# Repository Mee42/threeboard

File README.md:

## Threeboard

The v1 threeboard has been fully assembled and firmware is currently in developement. 
Firmware is in the `code/` directory and is written in C.

### KiCad instructions
PCB files are in the `pcb/` directory. Threeboard is designed on an ATSAMD21E17A arm microcontroller. A v2 board is in development

Both 
[random parts](https://github.com/ai03-2725/random-keyboard-parts.pretty)
and
[mx switch footprint](https://github.com/ai03-2725/MX_Alps_Hybrid.pretty)
are dependencies for the kicad files.

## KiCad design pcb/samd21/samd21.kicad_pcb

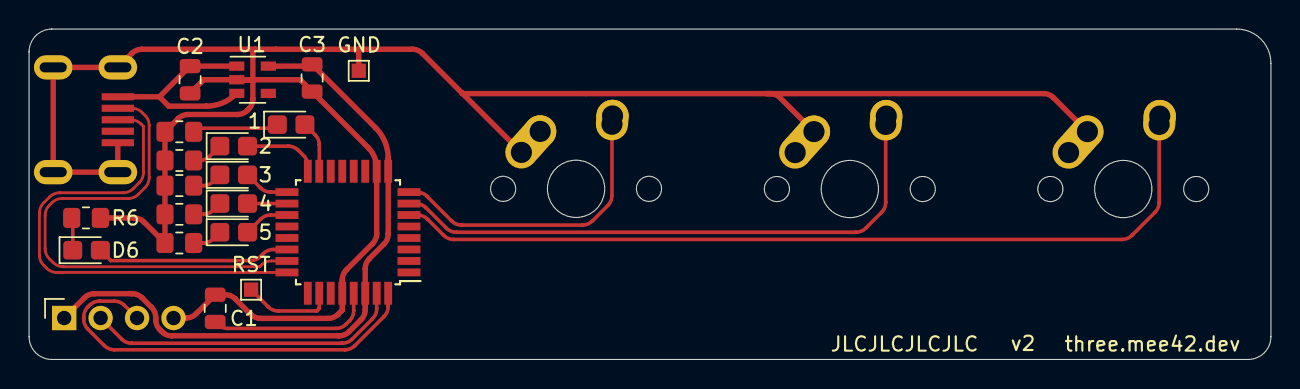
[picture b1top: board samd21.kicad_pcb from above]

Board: 2 copper layers, 86.5 x 23.0 mm, 24 parts (0 on the bottom side), 24 nets.

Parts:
1, 2, 3, 4, 5: LED; LED_0805_2012Metric_Castellated
C1, C2, C3: 1uF; C_0805_2012Metric
D6: LED; LED_0805_2012Metric_Castellated
GND: TestPoint; TestPoint_Pad_1.0x1.0mm
J1: Conn_01x04_Male; PinSocket_1x04_P2.54mm_Vertical
MX1, MX2, MX3: MX-NoLED; MX-1U-NoLED
R1, R2, R3, R4, R5, R6: 1.5K; R_0805_2012Metric_Pad1.20x1.40mm_HandSolder
RST: TestPoint; TestPoint_Pad_1.0x1.0mm
U1: TLV70033_SOT23-5; SOT-23-5
U2: ATSAMD21E17A-A; TQFP-32_7x7mm_P0.8mm
USB1: Molex-0548190589

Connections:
+3V3: C3.1, J1.1, U1.5 (OUT), U2.9 (VDDANA), U2.30 (VDDIN)
/5V: C2.1, U1.1 (IN), U1.3 (EN), USB1.5 (VBUS)
D+: U2.24 (PA25), USB1.3 (D+)
D-: U2.23 (PA24), USB1.4 (D-)
GND: C1.1, C2.2, C3.2, GND.1, J1.4, MX1.1 (COL), MX2.1 (COL), MX3.1 (COL), R1.2, R2.2, R3.2, R4.2, R5.2, R6.2, U1.2 (GND), U2.10 (GND), U2.28 (GND), USB1.1 (GND), USB1.6 (SHIELD)
KEY1: MX1.2 (ROW), U2.8 (PA07)
KEY2: MX2.2 (ROW), U2.7 (PA06)
KEY3: MX3.2 (ROW), U2.6 (PA05)
LED0: 1.2 (A), U2.15 (PA14)
LED1: 2.2 (A), U2.16 (PA15)
LED2: 3.2 (A), U2.17 (PA16)
LED3: 4.2 (A), U2.18 (PA17)
LED4: 5.2 (A), U2.19 (PA18)
LED5: D6.2 (A), U2.22 (PA23)
unnamed: C1.2, U2.29 (VDDCORE)
unnamed: 1.1 (K), R1.1
unnamed: 2.1 (K), R2.1
unnamed: 3.1 (K), R3.1
unnamed: 4.1 (K), R4.1
unnamed: 5.1 (K), R5.1
unnamed: D6.1 (K), R6.1
unnamed: RST.1, U2.26 (~RESET)
SWCLK: J1.2, U2.31 (PA30)
SWDIO: J1.3, U2.32 (PA31)

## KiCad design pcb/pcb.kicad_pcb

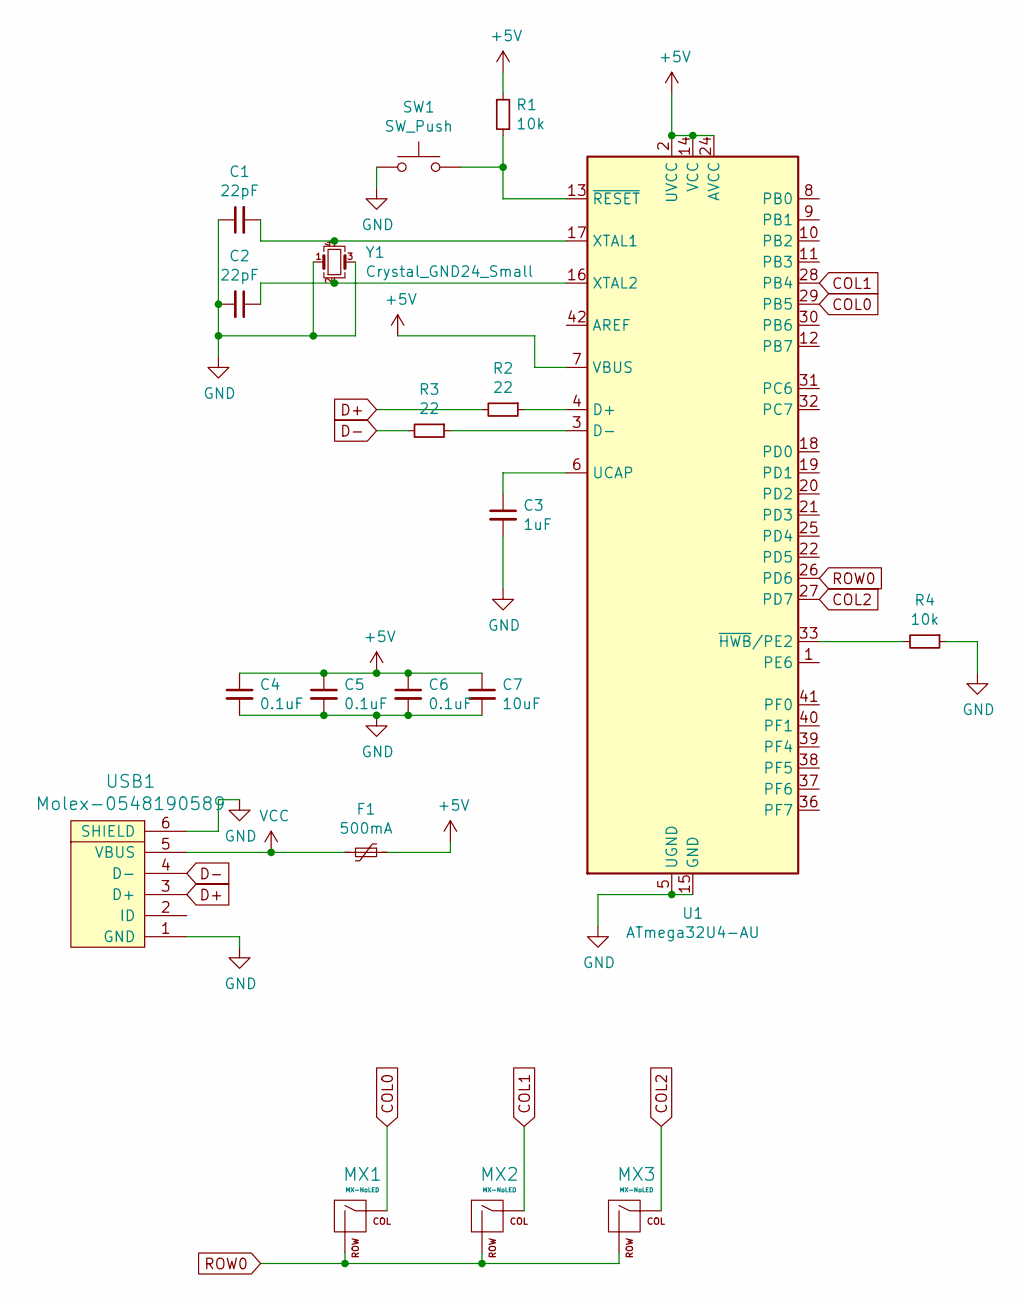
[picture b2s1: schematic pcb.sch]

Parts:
C1, C2: 22pF; C_0805_2012Metric
C3: 1uF; C_0805_2012Metric
C4, C5, C6: 0.1uF; C_0805_2012Metric
C7: 10uF; C_0805_2012Metric
F1: 500mA; Fuse_1206_3216Metric
MX1, MX2, MX3: MX-NoLED; MX-1U-NoLED
R1, R4: 10k; R_0805_2012Metric
R2, R3: 22; R_0805_2012Metric
SW1: SW_Push; SKQG-1155865
U1: ATmega32U4-AU; TQFP-44_10x10mm_P0.8mm
USB1: Molex-0548190589
Y1: Crystal_GND24_Small; Crystal_SMD_3225-4Pin_3.2x2.5mm

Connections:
+5V: C4.1, C5.1, C6.1, C7.1, F1.1, R1.1, U1.2 (UVCC), U1.7 (VBUS), U1.14 (VCC), U1.24 (AVCC), U1.34 (VCC), U1.44 (AVCC)
COL0: MX1.1 (COL), U1.29 (PB5)
COL1: MX2.1 (COL), U1.28 (PB4)
COL2: MX3.1 (COL), U1.27 (PD7)
D+: R2.2, USB1.3 (D+)
D-: R3.2, USB1.4 (D-)
GND: C1.1, C2.2, C3.2, C4.2, C5.2, C6.2, C7.2, R4.1, SW1.1, U1.5 (UGND), U1.15 (GND), U1.23 (GND), U1.35 (GND), U1.43 (GND), USB1.1 (GND), USB1.6 (SHIELD), Y1.1, Y1.3
unnamed: C1.2, U1.17 (XTAL1), Y1.4
unnamed: C2.1, U1.16 (XTAL2), Y1.2
unnamed: C3.1, U1.6 (UCAP)
unnamed: R1.2, SW1.2, U1.13 (~RESET)
unnamed: R2.1, U1.4 (D+)
unnamed: R3.1, U1.3 (D-)
unnamed: R4.2, U1.33 (~HWB~/PE2)
ROW0: MX1.2 (ROW), MX2.2 (ROW), MX3.2 (ROW), U1.26 (PD6)
VCC: F1.2, USB1.5 (VBUS)

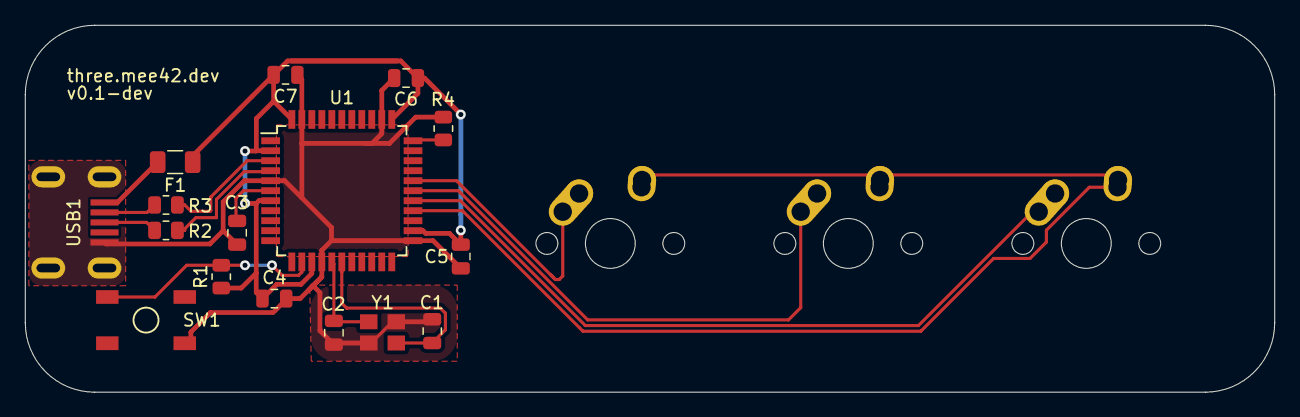
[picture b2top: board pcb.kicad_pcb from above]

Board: 2 copper layers, 100.0 x 29.4 mm, 19 parts (0 on the bottom side), 16 nets.

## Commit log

2021-07-03 added main.pywq
    qq# Please enter the commit message for your changes. Lines starting
2021-07-03 added explaination to readme
2021-07-03 added tree.svg
2021-07-03 proto1.jpg
2021-07-03 added "it works!"
2021-07-03 added 7 combos to readme.md
2021-07-07 added modifiers, logging, caps status lock, tree
2021-07-07 new tree
2021-07-21 started pcb project
2021-07-21 added submodules
2021-07-21 added submodules into pcb project
2021-07-21 schema?
2021-07-22 who tf knows anymore
2021-08-13 finished tracing pcb
2021-08-13 de v
2021-08-13 atmega v0.1?
2021-08-13 starting samd21 version
2021-08-13 fixed modules? who tf knows honestly
2021-08-13 working on samd21 model
2021-08-13 got most of the parts down..
2021-08-13 pinout updates
2021-08-14 v1-dev pcb+schem complete. not finished
2021-08-14 moved switches from 3v3 to GND, using pullup
2021-08-15 added python mockup for morse code reader
2021-08-17 pictures
2021-08-22 docs update in main.py
2021-08-22 docs!
2021-08-22 mode1 impl kinda
2021-08-22 docs
2021-08-22 cleaned repo
2021-08-22 readme
2021-08-22 pictures!
2021-08-23 testing gh pages
2021-08-23 html?
2021-08-23 modified: docs/index.html
2021-08-23 modified: docs/interface.pdf
2021-08-23 margins not cringe
2021-11-07 made arm work
2021-11-21 started working on c interop
2021-11-22 last commit before switching to C-only build
2021-11-22 started on C version of code, .data bork
2021-11-23 .data (should) work!
2021-11-23 cleaned up code
2021-11-24 blink 5 times on startup then strobe
2021-11-24 SUCCESS led is tied to switch
2021-11-24 cleaned
2021-11-24 removed all build artifacts
2021-11-25 playing around with v2 board ideas
2021-11-26 readme stuff
2021-11-26 cleaned up
